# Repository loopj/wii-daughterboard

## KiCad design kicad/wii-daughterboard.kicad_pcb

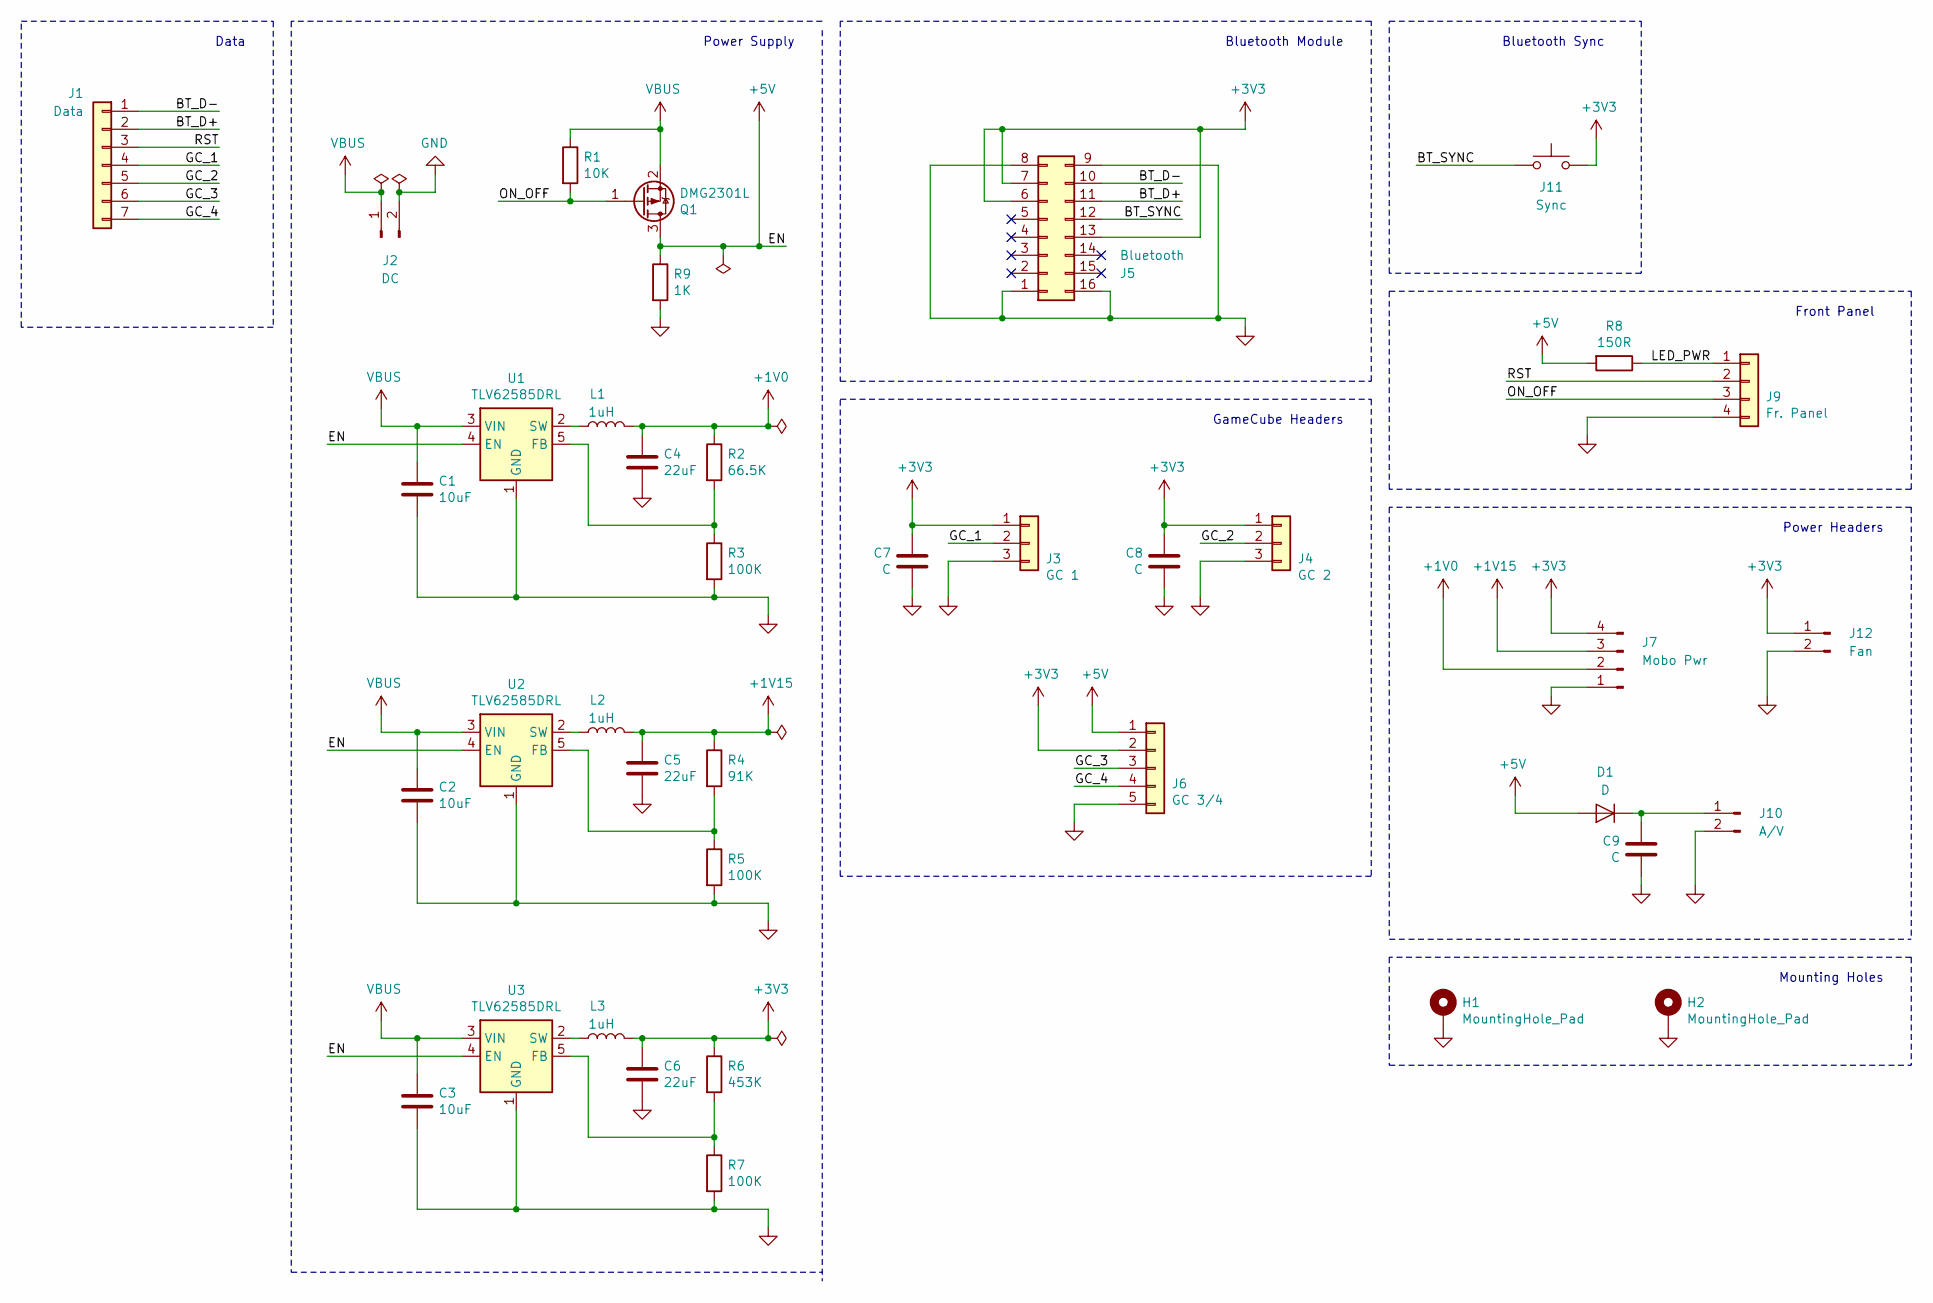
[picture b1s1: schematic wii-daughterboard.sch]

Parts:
C1, C2, C3: 10uF; C_0603_1608Metric_Pad1.05x0.95mm_HandSolder
C4, C5, C6: 22uF; C_0603_1608Metric_Pad1.05x0.95mm_HandSolder
C7, C8, C9: C; C_0603_1608Metric_Pad1.05x0.95mm_HandSolder
D1: D; D_SOD-123
H1, H2: MountingHole_Pad; MountingHole_2.7mm_Pad
J1: Data; JST_SH_BM07B-SRSS-TB_1x07-1MP_P1.00mm_Vertical
J2: DC; JST_PH_B2B-PH-SM4-TB_1x02-1MP_P2.00mm_Vertical
J3: GC 1; JST_SH_BM03B-SRSS-TB_1x03-1MP_P1.00mm_Vertical
J4: GC 2; JST_SH_BM03B-SRSS-TB_1x03-1MP_P1.00mm_Vertical
J5: Bluetooth; Wii_Bluetooth_Module
J6: GC 3/4; JST_SH_BM05B-SRSS-TB_1x05-1MP_P1.00mm_Vertical
J7: Mobo Pwr; JST_PH_S4B-PH-SM4-TB_1x04-1MP_P2.00mm_Horizontal
J9: Fr. Panel; SFV4R3STBE1HLF
J10: A/V; JST_SH_BM02B-SRSS-TB_1x02-1MP_P1.00mm_Vertical
J11: Sync; JST_SH_BM02B-SRSS-TB_1x02-1MP_P1.00mm_Vertical
J12: Fan; JST_SH_BM02B-SRSS-TB_1x02-1MP_P1.00mm_Vertical
L1, L2, L3: 1uH; INDPM3630X200N
Q1: DMG2301L; SOT-23_Handsoldering
R1: 10K; R_0603_1608Metric_Pad1.05x0.95mm_HandSolder
R2: 66.5K; R_0603_1608Metric_Pad1.05x0.95mm_HandSolder
R3, R5, R7: 100K; R_0603_1608Metric_Pad1.05x0.95mm_HandSolder
R4: 91K; R_0603_1608Metric_Pad1.05x0.95mm_HandSolder
R6: 453K; R_0603_1608Metric_Pad1.05x0.95mm_HandSolder
R8: 150R; R_0603_1608Metric_Pad1.05x0.95mm_HandSolder
R9: 1K; R_0603_1608Metric_Pad1.05x0.95mm_HandSolder
U1, U2, U3: TLV62585DRL; SOT-563

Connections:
+1V0: C4.1, J7.2, L1.2, R2.1
+1V15: C5.1, J7.3, L2.2, R4.1
+3V3: C6.1, C7.2, C8.2, J3.1, J4.1, J5.6, J5.7, J5.13, J6.2, J7.4, J11.2, J12.1, L3.2, R6.1
+5V: D1.2 (A), J6.1, Q1.3 (D), R8.2, R9.1, U1.4 (EN), U2.4 (EN), U3.4 (EN)
/BT_D+: J1.2, J5.11
/BT_D-: J1.1, J5.10
/BT_SYNC: J5.12, J11.1
/GC_1: J1.4, J3.2
/GC_2: J1.5, J4.2
/GC_3: J1.6, J6.3
/GC_4: J1.7, J6.4
/LED_PWR: J9.1, R8.1
/ON_OFF: J9.3, Q1.1 (G), R1.2
/RST: J1.3, J9.2
GND: C1.2, C2.2, C3.2, C4.2, C5.2, C6.2, C7.1, C8.1, C9.1, H1.1, H2.1, J2.2, J3.3, J4.3, J5.1, J5.8, J5.9, J5.16, J6.5, J7.1, J9.4, J10.2, J12.2, R3.2, R5.2, R7.2, R9.2, U1.1 (GND), U2.1 (GND), U3.1 (GND)
unnamed: C9.2, D1.1 (K), J10.1
unnamed: L1.1, U1.2 (SW)
unnamed: L2.1, U2.2 (SW)
unnamed: L3.1, U3.2 (SW)
unnamed: R2.2, R3.1, U1.5 (FB)
unnamed: R4.2, R5.1, U2.5 (FB)
unnamed: R6.2, R7.1, U3.5 (FB)
VBUS: C1.1, C2.1, C3.1, J2.1, Q1.2 (S), R1.1, U1.3 (VIN), U2.3 (VIN), U3.3 (VIN)

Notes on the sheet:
Power Supply
Bluetooth Module
GameCube Headers
Bluetooth Sync
Data
Front Panel
Power Headers
Mounting Holes

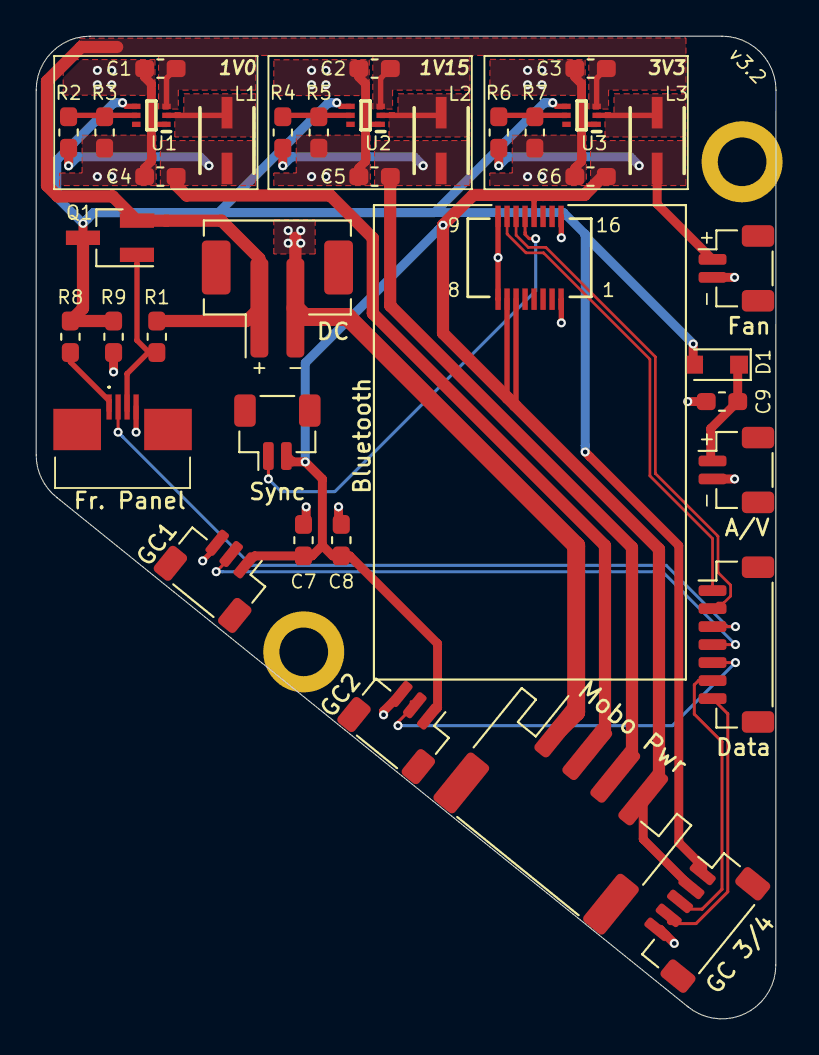
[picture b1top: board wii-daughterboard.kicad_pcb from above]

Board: 2 copper layers, 41.1 x 54.6 mm, 39 parts (0 on the bottom side), 23 nets.

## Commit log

2020-04-08 v2.0
2020-04-30 Fix mosfet bug
2020-05-10 Fix MOSFET orientation, add pulldown
2020-05-10 Change fan power to 3V3
2020-05-12 v3.0
2020-05-21 v3.1
2020-05-21 Single GND return from mobo
2020-05-21 Nicer diode label
2020-05-27 v3.2
